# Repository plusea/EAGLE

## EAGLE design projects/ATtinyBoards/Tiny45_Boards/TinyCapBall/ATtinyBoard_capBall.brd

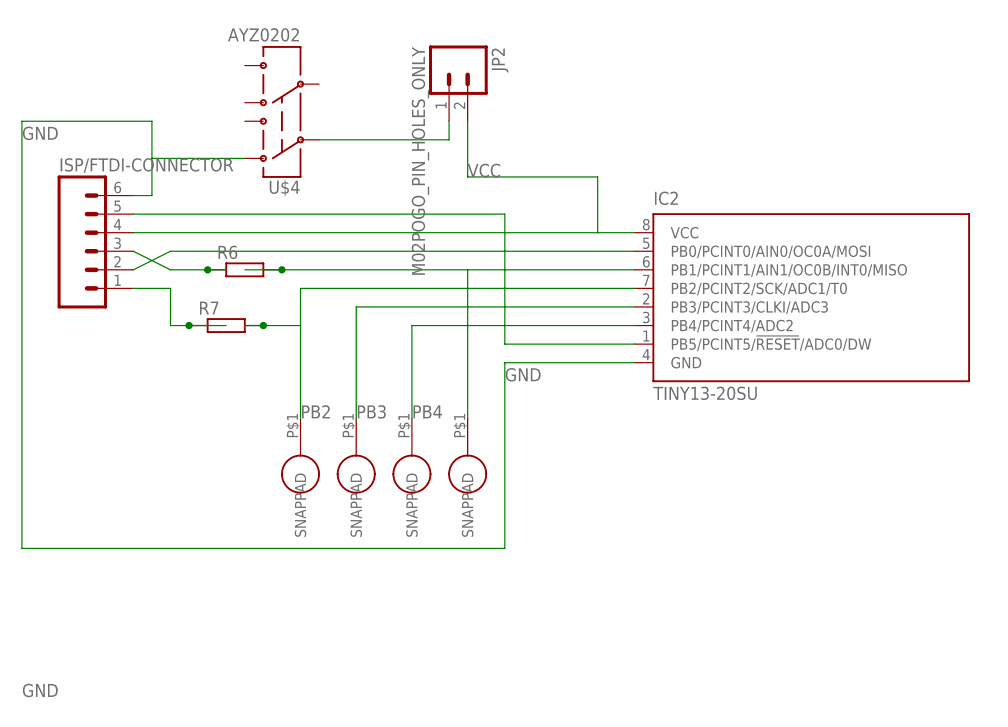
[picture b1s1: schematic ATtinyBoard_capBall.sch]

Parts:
IC2: TINY13-20SU; 8S2
ISP/FTDI-CONNECTOR: M06SMD; 1X06-SMD
JP2: M02POGO_PIN_HOLES_ONLY; 1X02_PP_HOLES_ONLY
R6, R7: R-EU_R2012; R2012
U$1, U$2, U$3, U$6: SNAP-PAD_7MM_ROUND; SNAP-PAD_7MM_RD
U$4: AYZ0202

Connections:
GND: IC2.4 (GND), ISP/FTDI-CONNECTOR.6, U$4.3 (1)
unnamed: IC2.5 (PB0/PCINT0/AIN0/OC0A/MOSI), ISP/FTDI-CONNECTOR.2
unnamed: ISP/FTDI-CONNECTOR.3, R6.1
unnamed: IC2.1 (PB5/PCINT5/!RESET!/ADC0/DW), ISP/FTDI-CONNECTOR.5
unnamed: IC2.6 (PB1/PCINT1/AIN1/OC0B/INT0/MISO), R6.2, U$6.P$1
unnamed: ISP/FTDI-CONNECTOR.1, R7.1
unnamed: JP2.1, U$4.2
PB2: IC2.7 (PB2/PCINT2/SCK/ADC1/T0), R7.2, U$1.P$1
PB3: IC2.2 (PB3/PCINT3/CLKI/ADC3), U$2.P$1
PB4: IC2.3 (PB4/PCINT4/ADC2), U$3.P$1
VCC: IC2.8 (VCC), ISP/FTDI-CONNECTOR.4, JP2.2

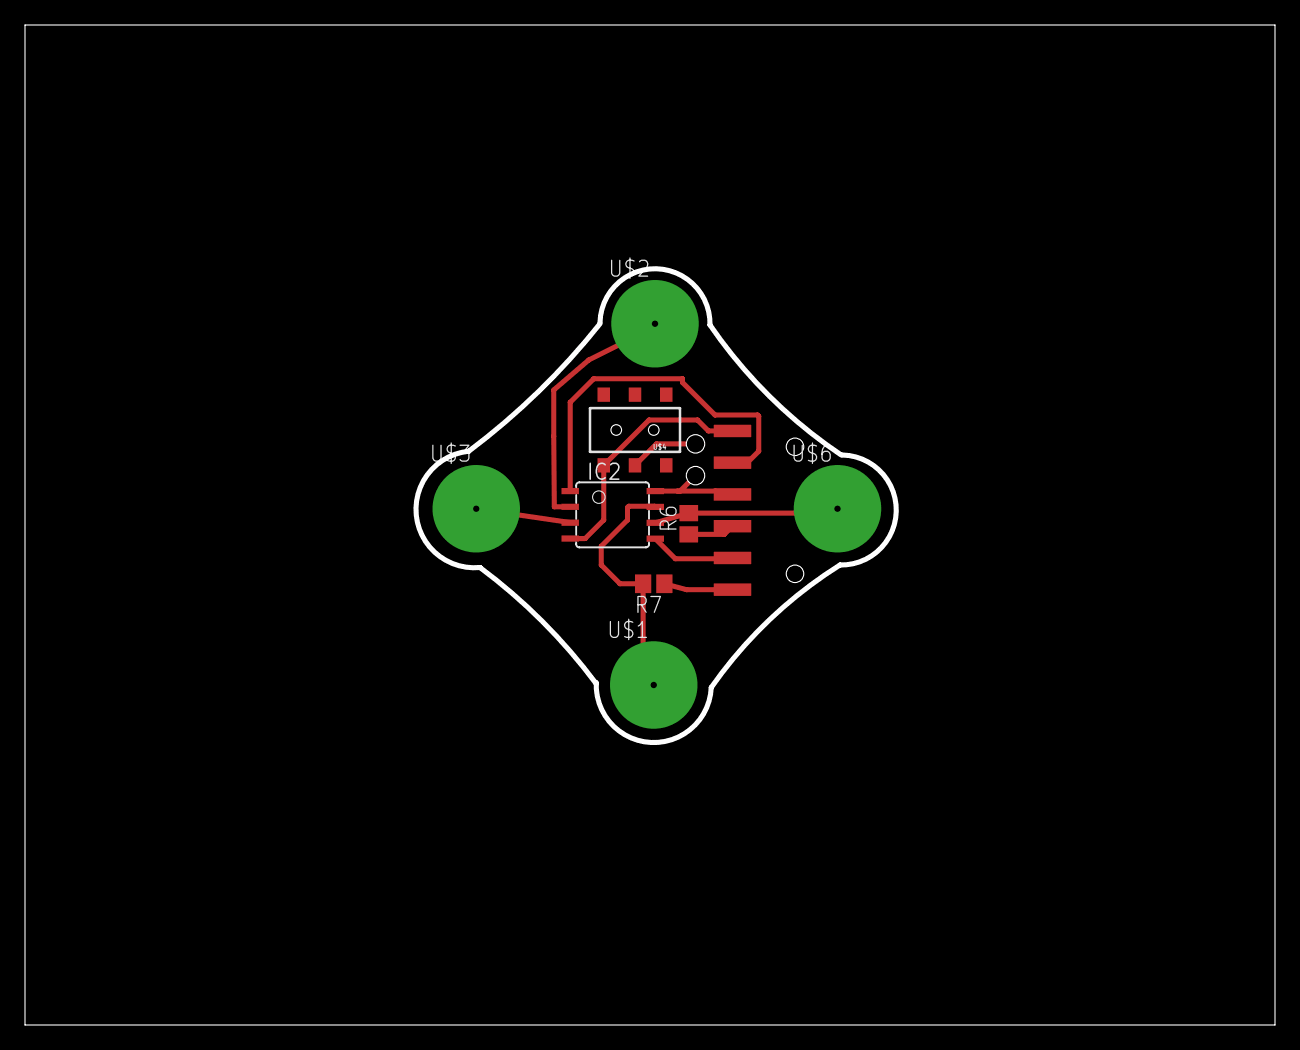
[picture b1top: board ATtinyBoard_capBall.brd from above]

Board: 2 copper layers, 100.0 x 80.0 mm, 10 parts (0 on the bottom side), 11 nets.

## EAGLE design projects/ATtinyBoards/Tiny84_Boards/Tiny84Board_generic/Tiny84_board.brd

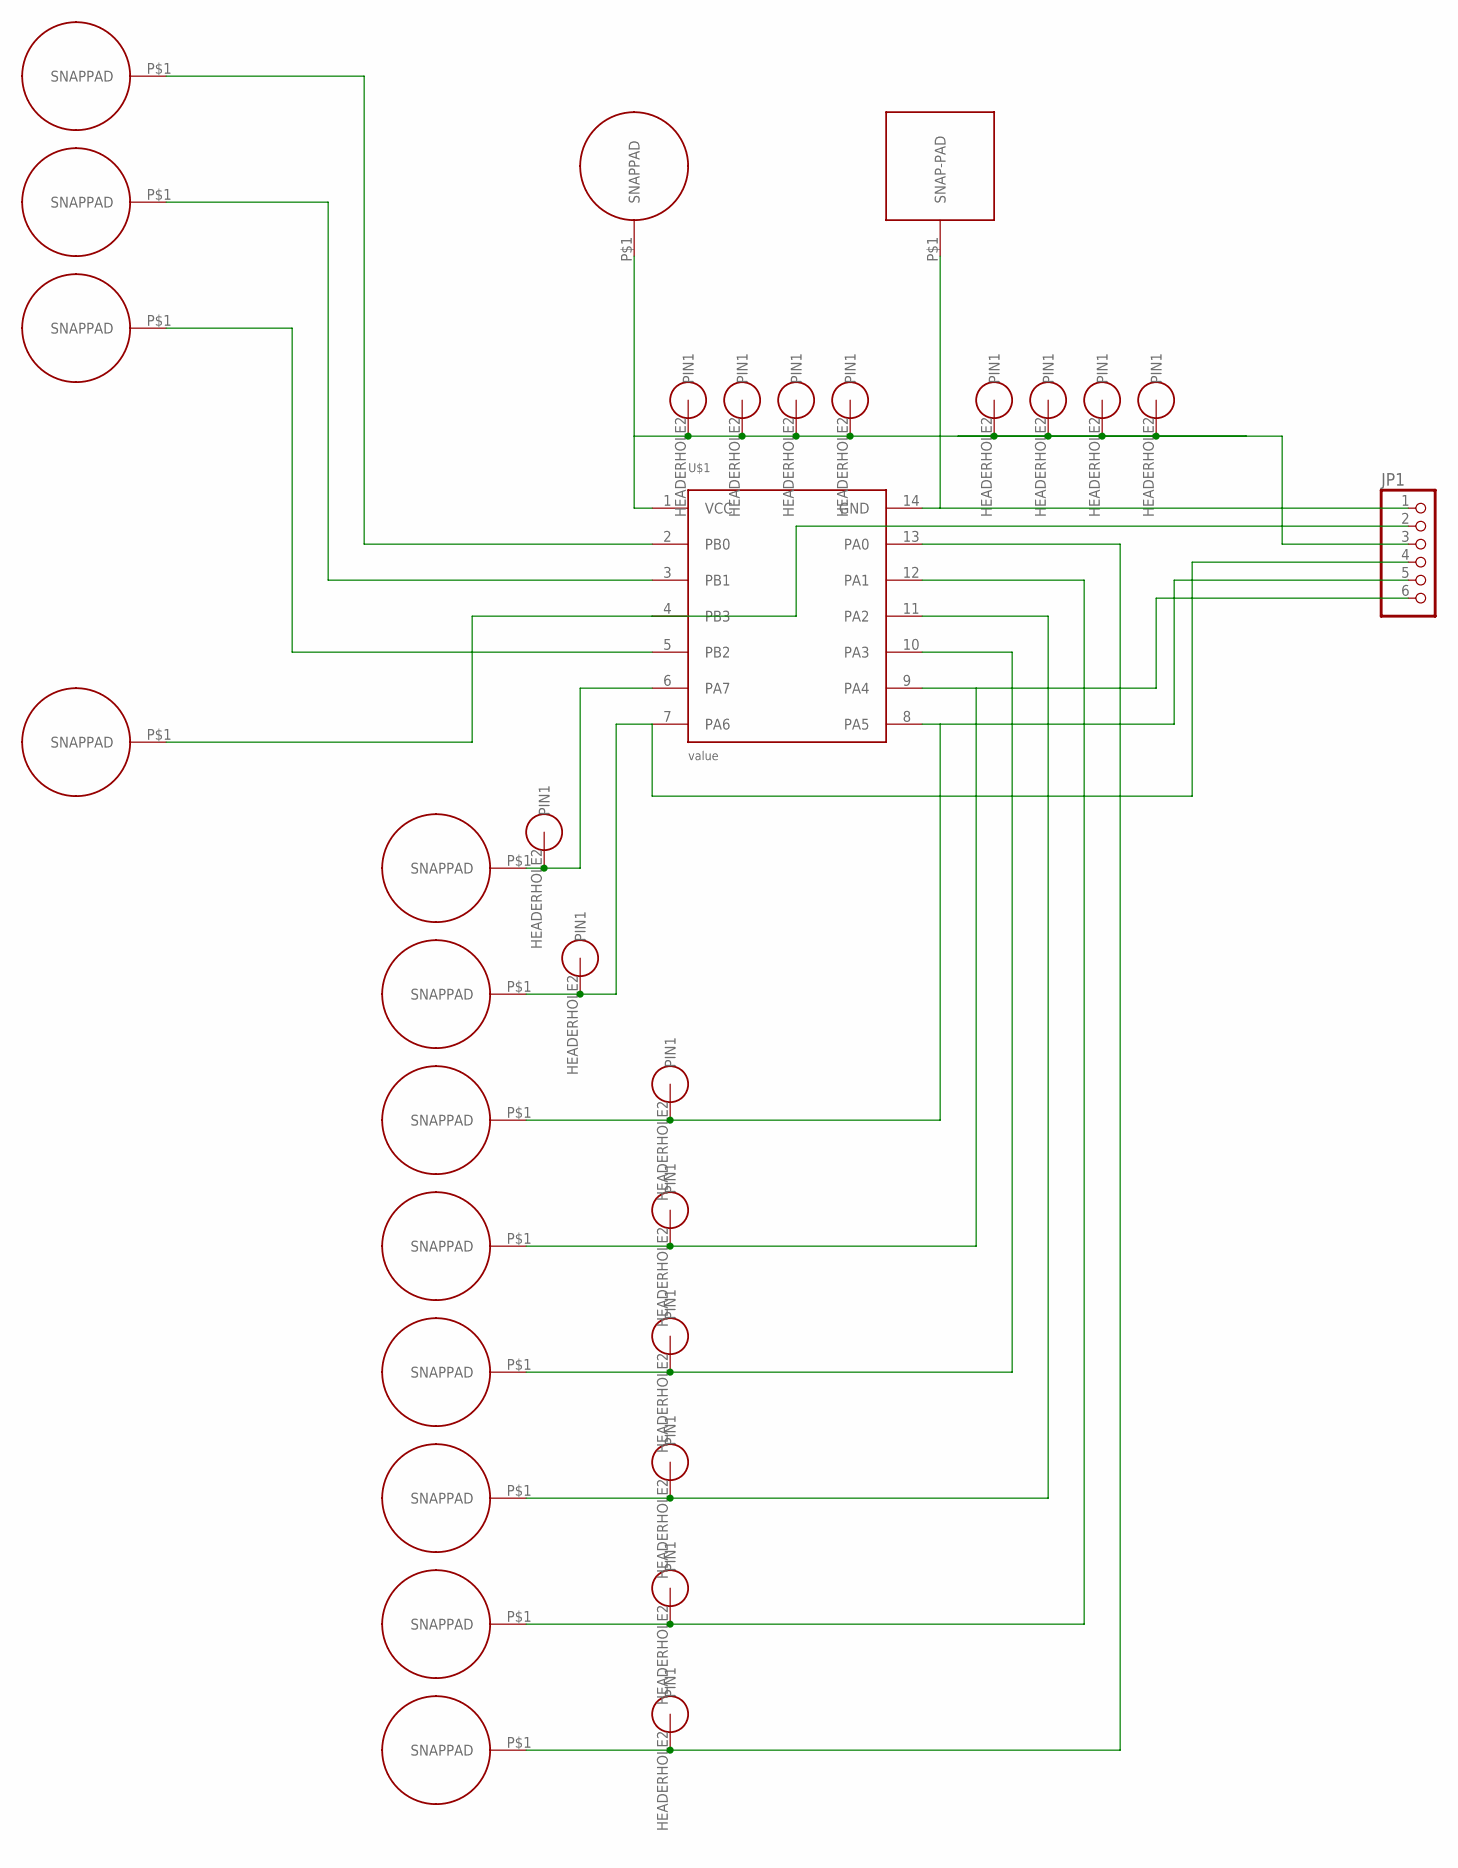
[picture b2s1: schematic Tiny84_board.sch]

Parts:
JP1: PINHD-1X6/90; 1X06/90
U$1: ATTINY84; SOIC14
U$2, U$3, U$4, U$5, U$6, U$7, U$8, U$9, U$10, U$11, U$12, U$13, U$18: SNAP-PAD_7MM_ROUND; SNAP-PAD_7MM_RD
U$14: SNAP-PAD_7MM_SQUARE; SNAP-PAD_7MM_SQ
U$15, U$16, U$17, U$19, U$20, U$21, U$22, U$23, U$24, U$25, U$26, U$27, U$28, U$29, U$30, U$31: HEADER_1PIN

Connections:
unnamed: JP1.1, U$1.14 (GND), U$14.P$1
unnamed: U$1.6 (PA7), U$2.P$1, U$27.HEADERHOLE2
unnamed: JP1.4, U$1.7 (PA6), U$3.P$1, U$26.HEADERHOLE2
unnamed: JP1.5, U$1.8 (PA5), U$4.P$1, U$17.HEADERHOLE2
unnamed: JP1.6, U$1.9 (PA4), U$5.P$1, U$19.HEADERHOLE2
unnamed: U$1.10 (PA3), U$6.P$1, U$20.HEADERHOLE2
unnamed: U$1.11 (PA2), U$7.P$1, U$21.HEADERHOLE2
unnamed: U$1.12 (PA1), U$8.P$1, U$22.HEADERHOLE2
unnamed: U$1.13 (PA0), U$9.P$1, U$23.HEADERHOLE2
unnamed: U$1.5 (PB2), U$13.P$1
unnamed: U$1.3 (PB1), U$12.P$1
unnamed: U$1.2 (PB0), U$11.P$1
unnamed: JP1.2, U$1.4 (PB3), U$18.P$1
VCC: JP1.3, U$1.1 (VCC), U$10.P$1, U$15.HEADERHOLE2, U$16.HEADERHOLE2, U$24.HEADERHOLE2, U$25.HEADERHOLE2, U$28.HEADERHOLE2, U$29.HEADERHOLE2, U$30.HEADERHOLE2, U$31.HEADERHOLE2

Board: 2 copper layers, 32 parts (0 on the bottom side), 14 nets, no tracks yet.

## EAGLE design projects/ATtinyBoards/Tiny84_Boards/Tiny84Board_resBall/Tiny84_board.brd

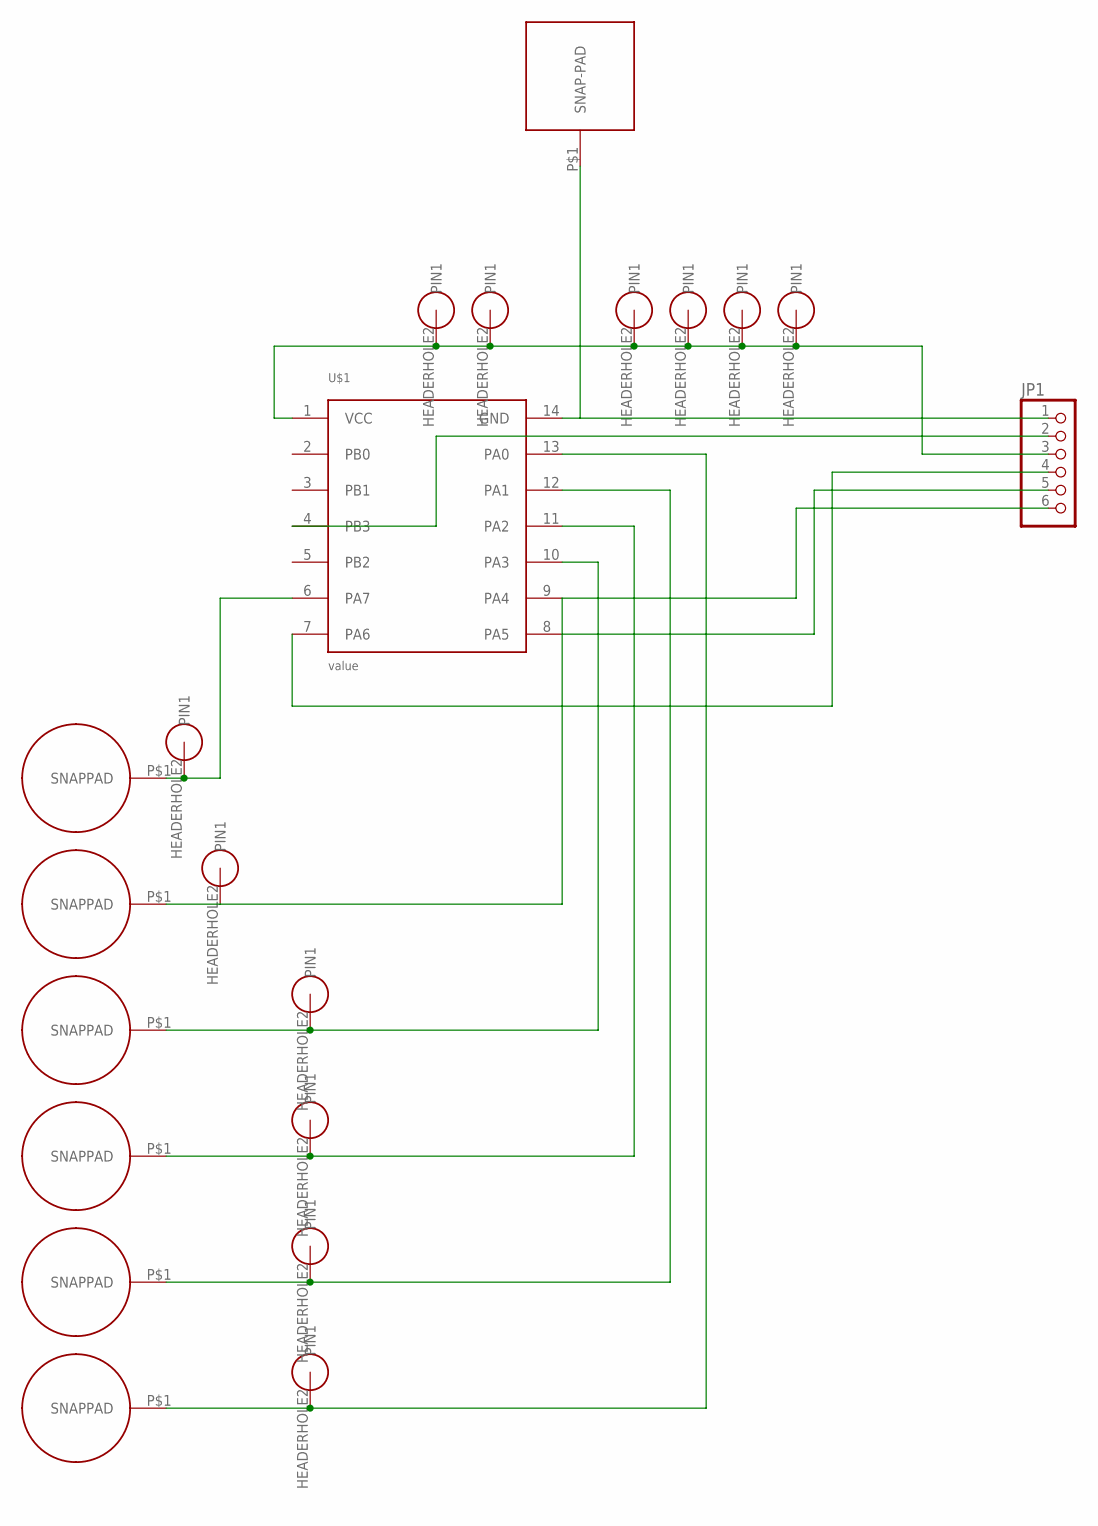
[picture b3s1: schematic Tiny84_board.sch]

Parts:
JP1: PINHD-1X6/90; 1X06/90
U$1: ATTINY84; SOIC14
U$2, U$3, U$4, U$5, U$6, U$7: SNAP-PAD_7MM_ROUND; SNAP-PAD_7MM_RD
U$14: SNAP-PAD_7MM_SQUARE; SNAP-PAD_7MM_SQ
U$15, U$16, U$17, U$19, U$20, U$21, U$24, U$25, U$26, U$27, U$30, U$31: HEADER_1PIN

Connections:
unnamed: JP1.1, U$1.14 (GND), U$14.P$1
unnamed: U$1.6 (PA7), U$2.P$1, U$27.HEADERHOLE2
unnamed: JP1.4, U$1.7 (PA6)
unnamed: JP1.5, U$1.8 (PA5)
unnamed: JP1.6, U$1.9 (PA4), U$3.P$1, U$26.HEADERHOLE2
unnamed: U$1.13 (PA0), U$7.P$1, U$21.HEADERHOLE2
unnamed: JP1.2, U$1.4 (PB3)
unnamed: U$1.12 (PA1), U$6.P$1, U$20.HEADERHOLE2
unnamed: U$1.10 (PA3), U$4.P$1, U$17.HEADERHOLE2
unnamed: U$1.11 (PA2), U$5.P$1, U$19.HEADERHOLE2
VCC: JP1.3, U$1.1 (VCC), U$15.HEADERHOLE2, U$16.HEADERHOLE2, U$24.HEADERHOLE2, U$25.HEADERHOLE2, U$30.HEADERHOLE2, U$31.HEADERHOLE2

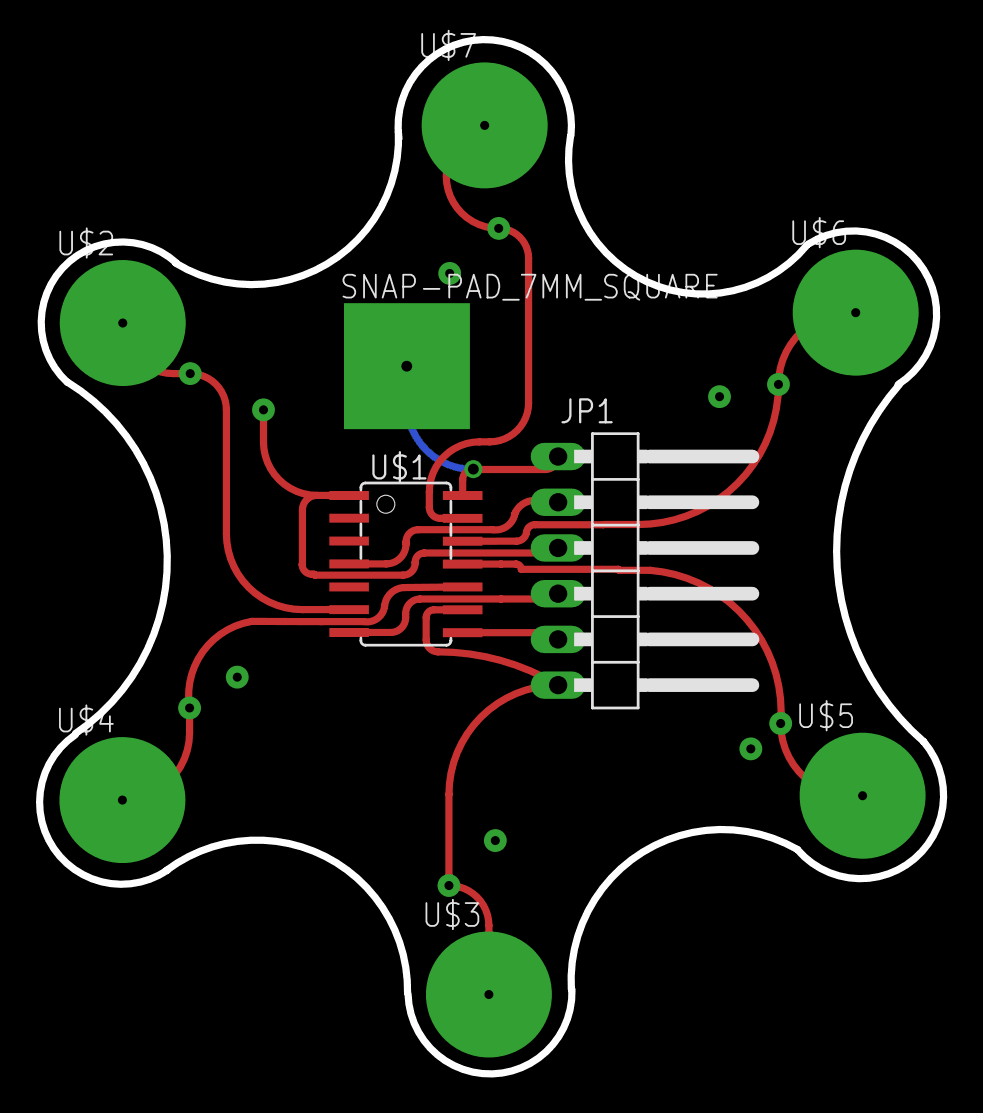
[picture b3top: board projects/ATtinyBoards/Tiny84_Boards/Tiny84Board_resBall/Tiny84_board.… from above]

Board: 2 copper layers, 50.2 x 57.5 mm, 21 parts (0 on the bottom side), 11 nets.

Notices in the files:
parts and their libraries:
SparkFun-Connectors: Licensing: CC v3.0 Share-Alike You are welcome to use this library for commercial purposes.
